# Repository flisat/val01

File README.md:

# #VAL01
_8 RGB Leds - Logic Gate - Motor_

## Parts
### 8 RGB leds
* When _LogOutPin1_ button is pushed, the 8 leds changed color one after other
* Color sequence : white -> red -> green -> blue -> off
* Illustration

### Logic Gate
* AND, OR and XOR logic gate with button _LogInPin1_ and _LogInPin2_
* Return in led _LogOutPin_
* Gate is changed randomly when _LogOutPin1_ is pushed
* Illustration

### Motor
Motor speed controled by a potentiometer.

## Arduino

## Kicad
### Schema

### PCB

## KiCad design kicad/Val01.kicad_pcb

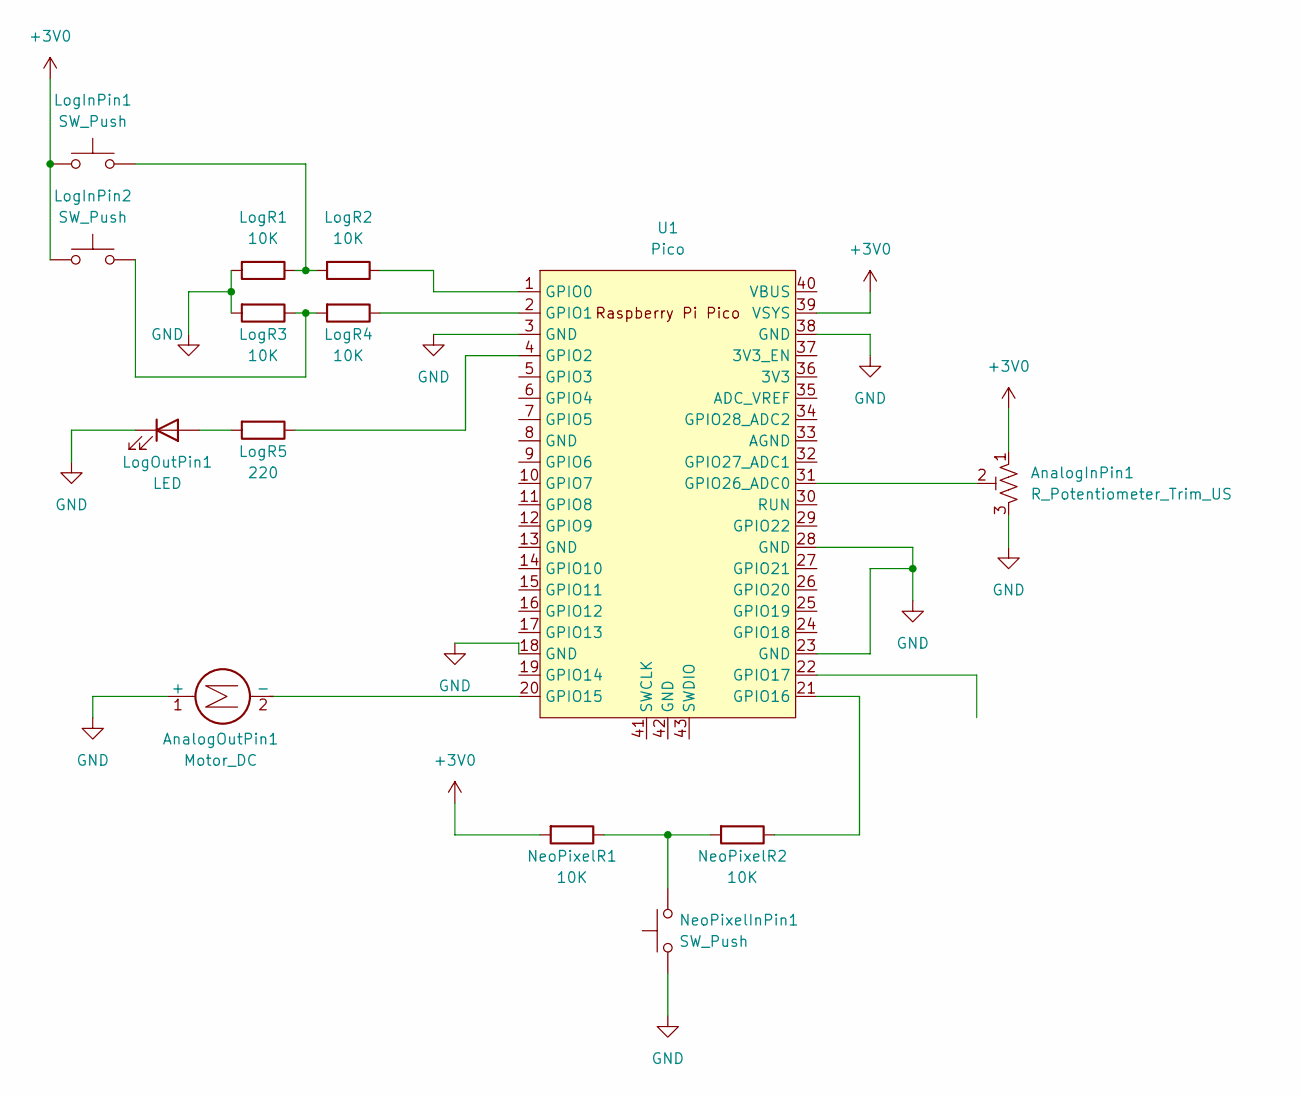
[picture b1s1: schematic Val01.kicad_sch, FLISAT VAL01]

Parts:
AnalogInPin1: R_Potentiometer_Trim_US; Potentiometer_Alps_RK163_Single_Horizontal
AnalogOutPin1: Motor_DC; SW_PUSH_6mm
LogInPin1, LogInPin2: SW_Push; SW_PUSH_6mm
LogOutPin1: LED; LED_D3.0mm
LogR1, LogR2, LogR3, LogR4: 10K; R_Axial_DIN0207_L6.3mm_D2.5mm_P15.24mm_Horizontal
LogR5: 220; R_Axial_DIN0207_L6.3mm_D2.5mm_P15.24mm_Horizontal
NeoPixelInPin1: SW_Push; SW_PUSH_6mm
NeoPixelR1, NeoPixelR2: 10K; R_Axial_DIN0207_L6.3mm_D2.5mm_P15.24mm_Horizontal
U1: Pico; RPi_Pico_SMD_TH

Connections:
+3V0: AnalogInPin1.1, LogInPin1.1, LogInPin2.1, NeoPixelR1.2, U1.39 (VSYS)
GND: AnalogInPin1.3, AnalogOutPin1.1 (+), LogOutPin1.1 (K), LogR1.2, LogR3.2, NeoPixelInPin1.1, U1.3 (GND), U1.18 (GND), U1.23 (GND), U1.28 (GND), U1.38 (GND)
unnamed: AnalogOutPin1.2 (-), U1.20 (GPIO15)
unnamed: LogInPin1.2, LogR1.1, LogR2.2
unnamed: LogInPin2.2, LogR3.1, LogR4.2
unnamed: LogOutPin1.2 (A), LogR5.2
unnamed: NeoPixelInPin1.2, NeoPixelR1.1, NeoPixelR2.2
unnamed: LogR2.1, U1.1 (GPIO0)
unnamed: LogR4.1, U1.2 (GPIO1)
unnamed: LogR5.1, U1.4 (GPIO2)
unnamed: NeoPixelR2.1, U1.21 (GPIO16)
unnamed: AnalogInPin1.2, U1.31 (GPIO26_ADC0)

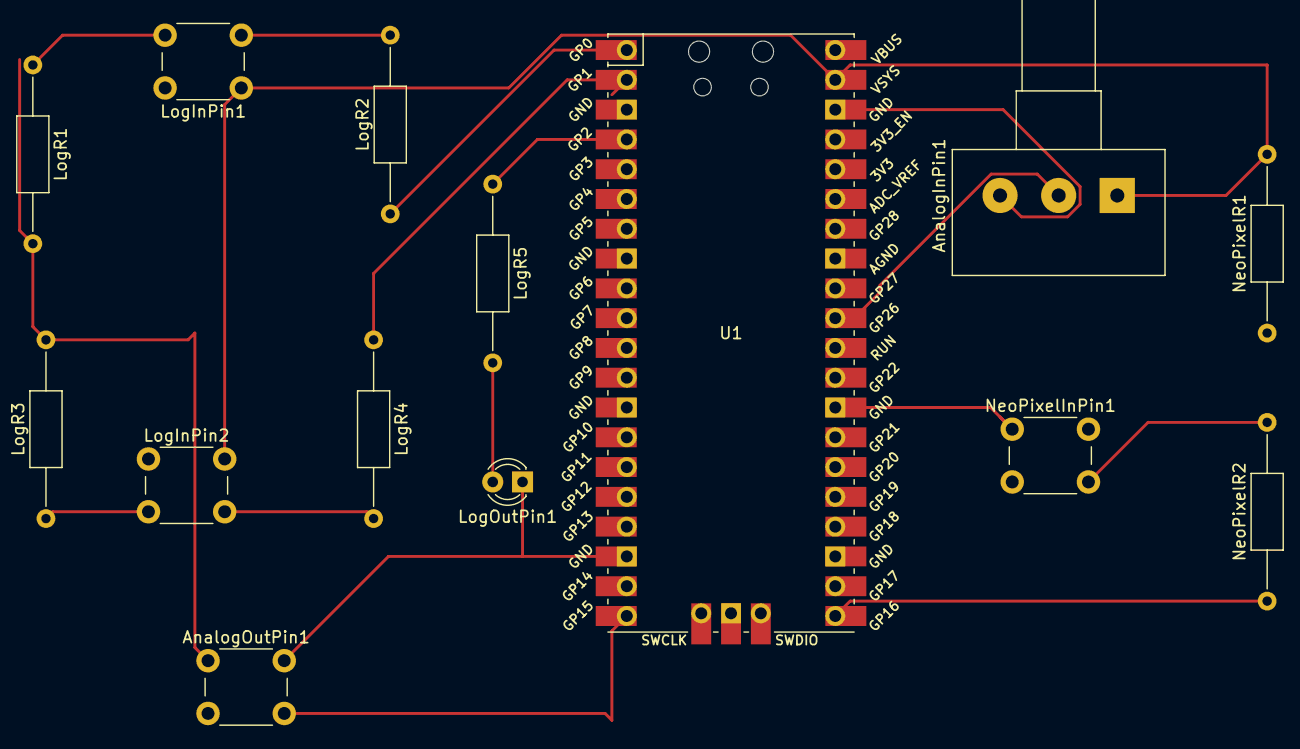
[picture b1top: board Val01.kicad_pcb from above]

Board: 2 copper layers, 14 parts (0 on the bottom side), 12 nets.

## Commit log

2023-11-19 change kicad dir name
2023-11-20 adding illustration for part 1 and 2
2023-11-20 update kicad
